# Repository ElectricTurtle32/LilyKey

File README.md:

# LilyKey
An opensource split wireless keyboard

This keyboard uses low profile Choc V2 switchs, and a XIAO nRF52840 with ZMK. 
The design fits together with only a few screws on the bottom

Firmware can be found in this 

OnShape link. In order to use the link, copy it into your browser, for some reason if you don't do that you get a 403 error.
https://cad.onshape.com/documents/438c57f3dff6ca4edb0a97ae/w/4621db7fe7b2abded9ecab59/e/34fd1f2b97a3de8af004570b

I will be buying the lubrication kit, and tribosys 3204 out of pocket, due to overbudget constraints. If required, I will also be buying the diodes and JST connectors out of pocket.\
BOM
| Description      | Link                                                                                                            | Qty. | Price Per Unit | Total Price |
| ---------------- | --------------------------------------------------------------------------------------------------------------- | ---- | -------------- | ----------- |
| JST PH connector | [LINK](https://www.digikey.com/en/products/detail/jst-sales-america-inc/S2B-PH-SM4-TB/926655)                   | 4    | $0.48          | $1.92       |
| Diodes           | [LINK](https://www.digikey.com/en/products/detail/smc-diode-solutions/1N4148W/6022450)                          | 100  | $0.05          | $4.74       |
| Switches         | [LINK](https://chosfox.com/products/kailh-four-seasons-mini-low-profile-linear-switches?variant=45837283131586) | 70   | $0.48          | $33.60      |
| XIAO nRF52840    | [LINK](https://www.seeedstudio.com/Seeed-Studio-XIAO-nRF52840-3PCS-p-5921.html)                                 | 2    | $9.90          | $19.80      |
| Battery          | [LINK](https://www.digikey.com/en/products/detail/adafruit-industries-llc/1578/5054539)                         | 2    | $7.95          | $15.90      |
| Lube (3204)      | [LINK](https://mech.land/products/tribosys-3204-lubricant-in-stock)                                             | 1    | $6.00          | $6.00       |
| Lubing Kit       | [LINK](https://chosfox.com/products/lubing-kit?variant=42670168473794)                                          | 1    | $5.00          | $5.00       |
| Keycaps          | [LINK](https://chosfox.com/products/chocfox-cfx-choc-keycaps?variant=42165428289730)                            | 7    | $3.50          | $24.50      |
|                  |                                                                                                                 |      |                | Total cost  |
|                  |                                                                                                                 |      |                | $111.46     |

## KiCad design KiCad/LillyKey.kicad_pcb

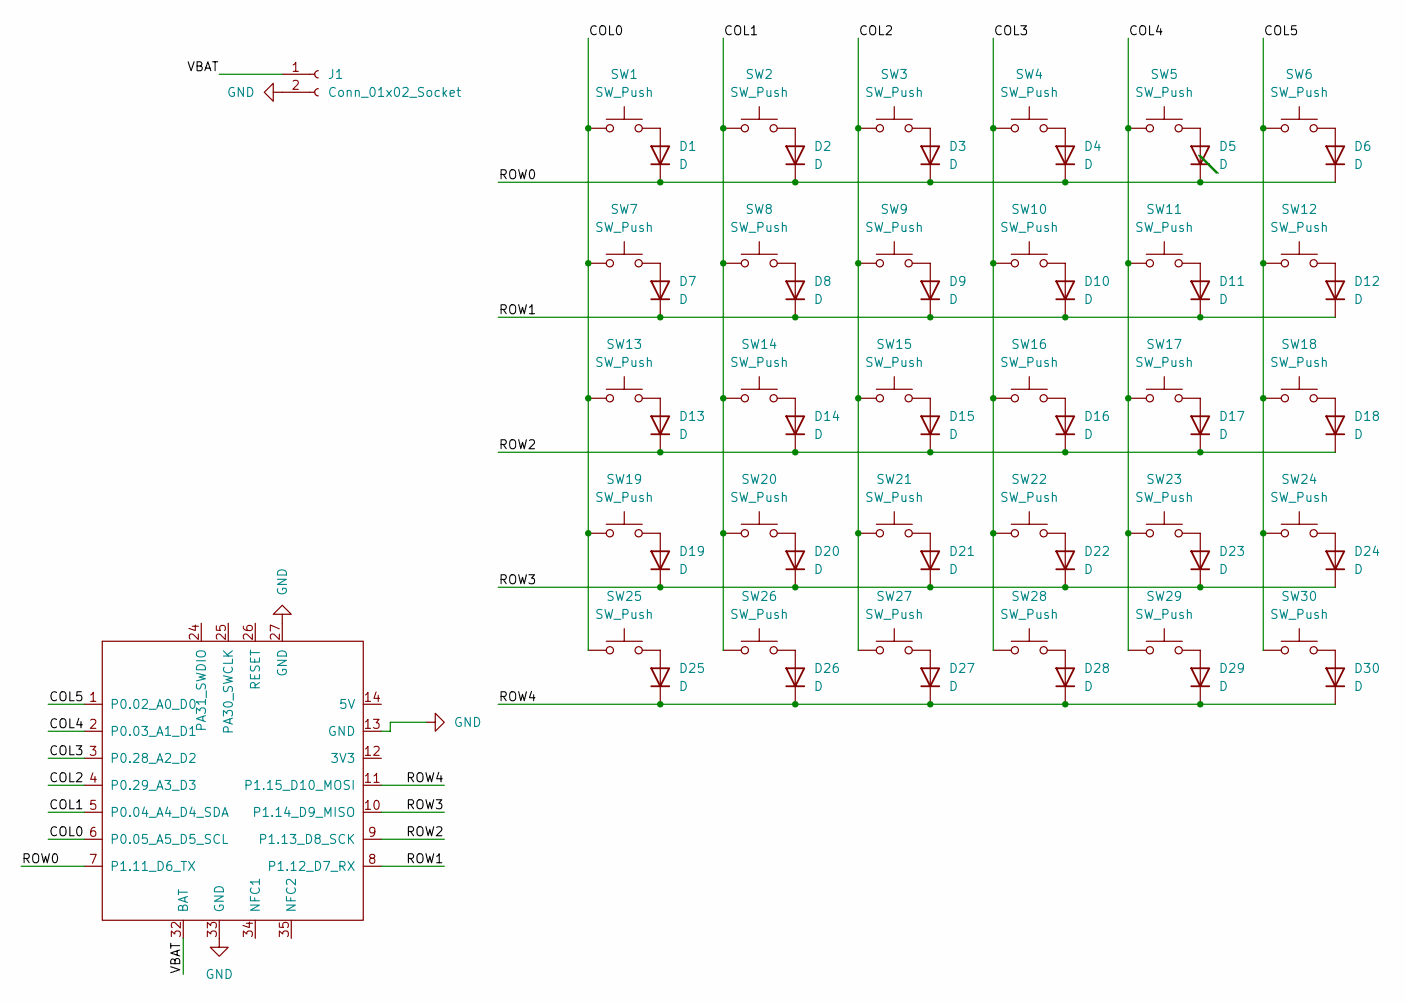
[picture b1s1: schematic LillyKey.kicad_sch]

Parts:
D1, D2, D3, D4, D5, D6, D7, D8, D9, D10, D11, D12, D13, D14, D15, D16, D17, D18, D19, D20, D21, D22, D23, D24, D25, D26, D27, D28, D29, D30: D; RevDiode
J1: Conn_01x02_Socket; JSTPH
SW1, SW2, SW3, SW4, SW5, SW6, SW7, SW8, SW9, SW10, SW11, SW12, SW13, SW14, SW15, SW16, SW17, SW18, SW19, SW20, SW21, SW22, SW23, SW24, SW25, SW26, SW27, SW28, SW29, SW30: SW_Push; SW_Hotswap_Kailh_Choc_V1V2
U2: XIAO-nRF52840-SMD; XIAO_nRF52840_DUAL

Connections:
/COL0: SW1.1, SW7.1, SW13.1, SW19.1, SW25.1, U2.6 (P0.05_A5_D5_SCL)
/COL1: SW2.1, SW8.1, SW14.1, SW20.1, SW26.1, U2.5 (P0.04_A4_D4_SDA)
/COL2: SW3.1, SW9.1, SW15.1, SW21.1, SW27.1, U2.4 (P0.29_A3_D3)
/COL3: SW4.1, SW10.1, SW16.1, SW22.1, SW28.1, U2.3 (P0.28_A2_D2)
/COL4: SW5.1, SW11.1, SW17.1, SW23.1, SW29.1, U2.2 (P0.03_A1_D1)
/COL5: SW6.1, SW12.1, SW18.1, SW24.1, SW30.1, U2.1 (P0.02_A0_D0)
/ROW0: D1.1 (K), D2.1 (K), D3.1 (K), D4.1 (K), D5.1 (K), D6.1 (K), U2.7 (P1.11_D6_TX)
/ROW1: D7.1 (K), D8.1 (K), D9.1 (K), D10.1 (K), D11.1 (K), D12.1 (K), U2.8 (P1.12_D7_RX)
/ROW2: D13.1 (K), D14.1 (K), D15.1 (K), D16.1 (K), D17.1 (K), D18.1 (K), U2.9 (P1.13_D8_SCK)
/ROW3: D19.1 (K), D20.1 (K), D21.1 (K), D22.1 (K), D23.1 (K), D24.1 (K), U2.10 (P1.14_D9_MISO)
/ROW4: D25.1 (K), D26.1 (K), D27.1 (K), D28.1 (K), D29.1 (K), D30.1 (K), U2.11 (P1.15_D10_MOSI)
/VBAT: J1.1, U2.32 (BAT)
GND: J1.2, U2.13 (GND), U2.27 (GND), U2.33 (GND)
unnamed: D1.2 (A), SW1.2
unnamed: D2.2 (A), SW2.2
unnamed: D3.2 (A), SW3.2
unnamed: D4.2 (A), SW4.2
unnamed: D5.2 (A), SW5.2
unnamed: D6.2 (A), SW6.2
unnamed: D7.2 (A), SW7.2
unnamed: D8.2 (A), SW8.2
unnamed: D9.2 (A), SW9.2
unnamed: D10.2 (A), SW10.2
unnamed: D11.2 (A), SW11.2
unnamed: D12.2 (A), SW12.2
unnamed: D13.2 (A), SW13.2
unnamed: D14.2 (A), SW14.2
unnamed: D15.2 (A), SW15.2
unnamed: D16.2 (A), SW16.2
unnamed: D17.2 (A), SW17.2
unnamed: D18.2 (A), SW18.2
unnamed: D19.2 (A), SW19.2
unnamed: D20.2 (A), SW20.2
unnamed: D21.2 (A), SW21.2
unnamed: D22.2 (A), SW22.2
unnamed: D23.2 (A), SW23.2
unnamed: D24.2 (A), SW24.2
unnamed: D25.2 (A), SW25.2
unnamed: D26.2 (A), SW26.2
unnamed: D27.2 (A), SW27.2
unnamed: D28.2 (A), SW28.2
unnamed: D29.2 (A), SW29.2
unnamed: D30.2 (A), SW30.2

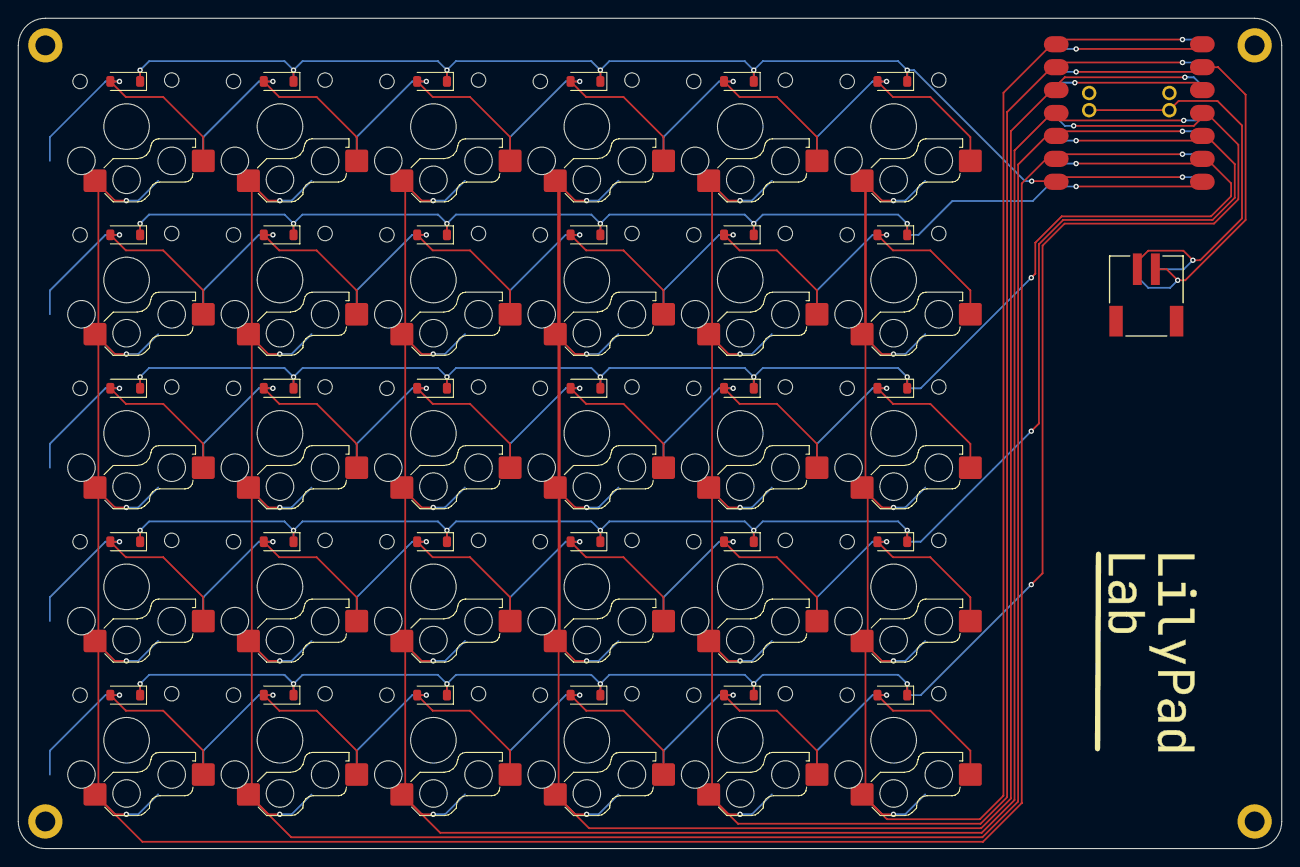
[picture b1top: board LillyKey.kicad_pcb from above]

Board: 2 copper layers, 140.0 x 92.0 mm, 62 parts (1 on the bottom side), 42 nets.

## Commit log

2026-01-24 Add KiCad
2026-01-24 Add image
2026-01-24 Enhance README with image and keyboard details
    Added an image and additional details about the keyboard's components and design.
2026-01-24 Figured out images
2026-01-24 Add images to README for better visualization
    Added images to enhance the README documentation.
2026-01-24 Add case files
2026-01-24 Add BOM section with component details to README
    Added a Bill of Materials (BOM) section with links and pricing for components.
2026-01-24 Add extra image
    Added a BOM section with details and a link to a JST PH connector.
2026-01-24 Update README with firmware repository link
    Added link to firmware repository in README.
2026-01-26 Update README with new images and BOM details
    Added additional images and updated BOM section with new information.
2026-01-26 Update images in README.md
    Replaced an image in the README with a new one and added an additional image.
2026-01-26 Fix up readme (ill fix tree somday I promise)
2026-01-26 Update funding details in README
    Clarified funding source for lubrication kit and components.
2026-02-02 Fliped around keys, cleanup
2026-02-02 New images
2026-02-05 Change Battery
2026-02-09 Remove 1 xiao
2026-02-12 Fix links in README for CAD files and firmware
    Updated links for CAD files and firmware repository in README.
2026-02-12 added firmware submod
2026-02-12 Update README with OnShape link and BOM information
    Added OnShape link and updated BOM details.
2026-02-12 Add onshape like for real
    Updated OnShape link formatting and added a brief note on purchasing components.
2026-02-12 Onshape is broken
    Removed the link to the Onshape document from the README.
2026-02-12 Add OnShape link to README
    Added OnShape link for CAD documentation.
2026-02-12 Update README with OnShape link instructions
    Clarify instructions for accessing OnShape link and mention out-of-pocket purchases for components.
2026-02-12 Removed v1 holes
